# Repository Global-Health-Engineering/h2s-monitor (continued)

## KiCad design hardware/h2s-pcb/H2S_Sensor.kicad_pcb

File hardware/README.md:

# Hardware

All hardware design files for the H2S sensor system, including the custom PCB and the 3D-printed enclosure and gas flow chamber.

## Structure

```
hardware/
├── design/
└── testing/
```

## System Overview

The hardware consists of three main physical components:

**Custom PCB** — designed in KiCad and manufactured by JLCPCB. Integrates the Seeed XIAO ESP32-C6 microcontroller, TI LMP91002 electrochemical analog front end, TI ADS1115 16-bit ADC, DS3232M RTC, SSD1306 OLED display, TI BQ25185 power management IC (USB-C charging, battery protection), MicroSD card slot, and N-channel MOSFET pump driver.

**3D-printed enclosure** — two-part PLA shell (bottom houses PCB, top carries display). Openings provide access to USB-C port, power button, MicroSD slot, and tube connectors.

**3D-printed flow chamber** — cylindrical chamber that seals around the electrochemical sensor body via an O-ring. A small internal cavity between the sensor face and the chamber top is flushed continuously by the diaphragm pump. Must be printed in resin for a gas-tight seal in field deployment; PLA is acceptable for bench testing only.

## Known Issues

- PCB revision V5 has a routing error on two of the four SPI lines to the MicroSD card, causing a short circuit that prevents SD card communication. SD logging is non-functional until corrected in the next revision.

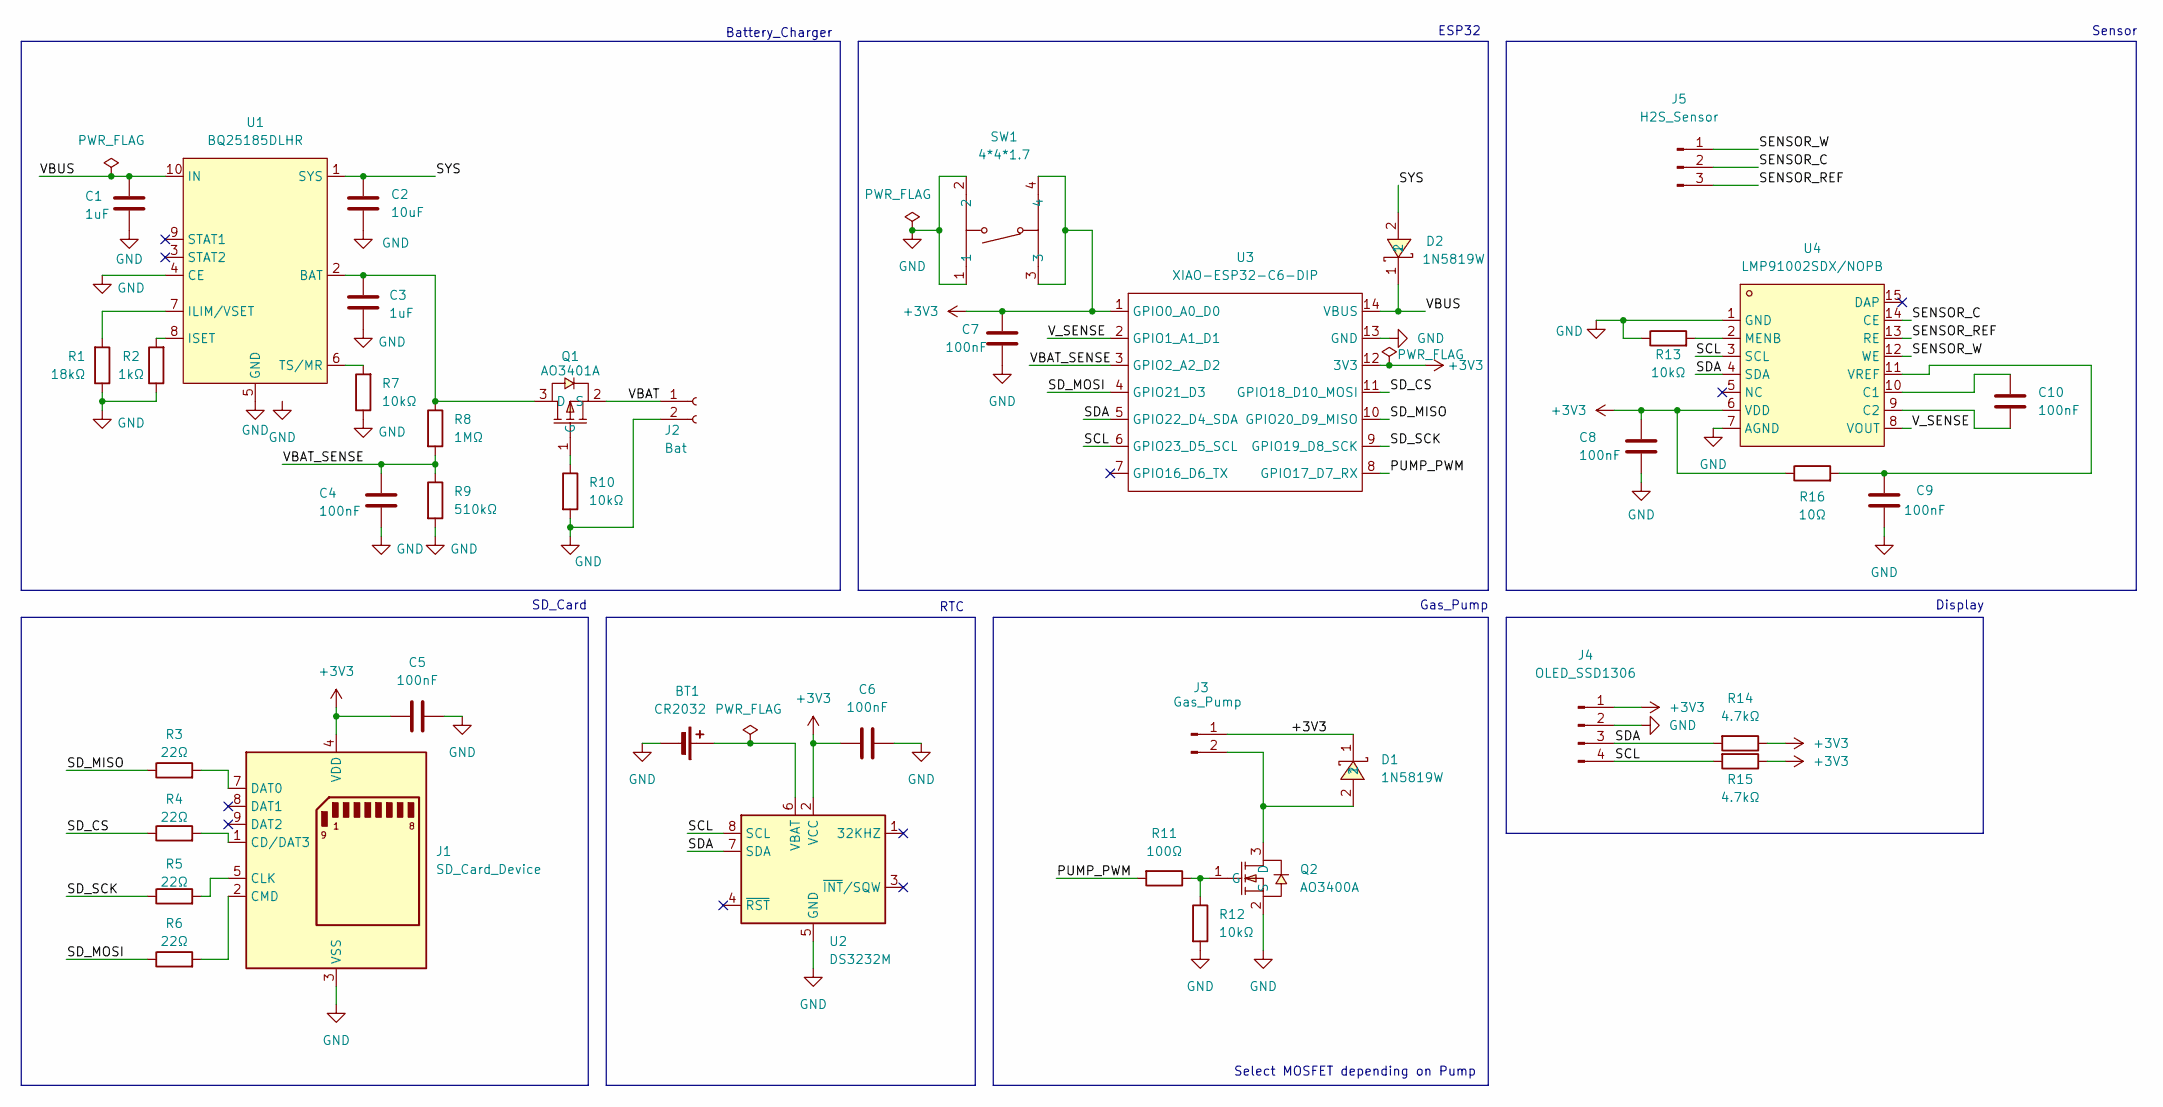
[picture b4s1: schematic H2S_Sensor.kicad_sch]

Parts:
BT1: CR2032; BAT-TH_CR2032-BS-6-1; LCSC Part C70377
C1, C3: 1uF; C_0603_1608Metric; LCSC Part C15849
C2: 10uF; C_0603_1608Metric; LCSC Part C96446
C4, C5, C6, C7, C8, C9, C10: 100nF; C_0603_1608Metric; LCSC Part C14663
D1, D2: 1N5819W; SOD-123F_L2.8-W1.8-LS3.7-RD; MPN 1N5819W; LCSC Part C169540
J1: SD_Card_Device; TF-SMD_TF-15-15; LCSC Part C111196
J2: Bat; Hirose_DF13-02P-1.25DSA_1x02_P1.25mm_Vertical
J3: Gas_Pump; Hirose_DF13-02P-1.25DSA_1x02_P1.25mm_Vertical
J4: OLED_SSD1306; Hirose_DF13-04P-1.25DSA_1x04_P1.25mm_Vertical
J5: H2S_Sensor; H2S_Sensor_3Pin_D20mm
Q1: AO3401A; SOT-23_L2.9-W1.3-P1.90-LS2.4-BR; MPN AO3401A; LCSC Part C15127
Q2: AO3400A; SOT-23-3_L2.9-W1.3-P1.90-LS2.4-BR; MPN AO3400A; LCSC Part C20917
R1: 18kΩ; R_0603_1608Metric; LCSC Part C25810
R2: 1kΩ; R_0603_1608Metric; LCSC Part C21190
R3, R4, R5, R6: 22Ω; R_0603_1608Metric; LCSC Part C23345
R7, R10, R12, R13: 10kΩ; R_0603_1608Metric; LCSC Part C25804
R8: 1MΩ; R_0603_1608Metric; LCSC Part C22935
R9: 510kΩ; R_0603_1608Metric; LCSC Part C23192
R11: 100Ω; R_0603_1608Metric; LCSC Part C22775
R14, R15: 4.7kΩ; R_0603_1608Metric; LCSC Part C23162
R16: 10Ω; R_0603_1608Metric; LCSC Part C22859
SW1: 4*4*1.7; SW-SMD_4P-L5.2-W5.2-P3.70-LS6.5; MPN 4*4*1.7 贴片; LCSC Part C10852
U1: BQ25185DLHR; WSON-10_L2.2-W2.0-P0.40-BL-EP_TI_DLH0010A; LCSC C19725033
U2: DS3232M; SOIC-8_3.9x4.9mm_P1.27mm; LCSC Part C2651581
U3: XIAO-ESP32-C6-DIP
U4: LMP91002SDX/NOPB; WSON-14_L4.0-W4.0-P0.50-BL-EP; MPN LMP91002SDX/NOPB; LCSC Part C2651581

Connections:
+3V3: C5.1, C6.2, C7.1, C8.1, D1.1, J1.4 (VDD), J3.1, J4.1, R14.1, R15.1, R16.1, SW1.3, SW1.4, U2.2 (VCC), U3.1 (GPIO0_A0_D0), U3.12 (3V3), U4.6 (VDD)
/PUMP_PWM: R11.2, U3.8 (GPIO17_D7_RX)
/SCL: J4.4, R15.2, U2.8 (SCL), U3.6 (GPIO23_D5_SCL), U4.3 (SCL)
/SDA: J4.3, R14.2, U2.7 (SDA), U3.5 (GPIO22_D4_SDA), U4.4 (SDA)
/SD_CS: R4.1, U3.11 (GPIO18_D10_MOSI)
/SD_MISO: R3.1, U3.10 (GPIO20_D9_MISO)
/SD_MOSI: R6.1, U3.4 (GPIO21_D3)
/SD_SCK: R5.1, U3.9 (GPIO19_D8_SCK)
/SENSOR_C: J5.2, U4.14 (CE)
/SENSOR_REF: J5.3, U4.13 (RE)
/SENSOR_W: J5.1, U4.12 (WE)
/SYS: C2.1, D2.2, U1.1 (SYS)
/VBAT: J2.1, Q1.2 (S)
/VBAT_SENSE: C4.1, R8.2, R9.1, U3.3 (GPIO2_A2_D2)
/VBUS: C1.2, D2.1, U1.10 (IN), U3.14 (VBUS)
/V_SENSE: U3.2 (GPIO1_A1_D1), U4.8 (VOUT)
GND: BT1.2 (-), C1.1, C2.2, C3.1, C4.2, C5.2, C6.1, C7.2, C8.2, C9.2, J1.3 (VSS), J1.6 (VSS), J2.2, J4.2, Q2.2 (S), R1.1, R2.1, R7.1, R9.2, R10.2, R12.2, R13.1, SW1.1, SW1.2, U1.4 (CE), U1.5 (GND), U1.11 (VSS), U2.5 (GND), U3.13 (GND), U4.1 (GND), U4.7 (AGND), U4.15 (DAP)
unnamed: BT1.1 (+), U2.6 (VBAT)
unnamed: J1.1 (CD/DAT3), R4.2
unnamed: J1.5 (CLK), R5.2
unnamed: J1.2 (CMD), R6.2
unnamed: J1.7 (DAT0), R3.2
unnamed: D1.2, J3.2, Q2.3 (D)
unnamed: C3.2, Q1.3 (D), R8.1, U1.2 (BAT)
unnamed: Q1.1 (G), R10.1
unnamed: Q2.1 (G), R11.1, R12.1
unnamed: R1.2, U1.7 (ILIM/VSET)
unnamed: R2.2, U1.8 (ISET)
unnamed: R7.2, U1.6 (TS/MR)
unnamed: C10.1, U4.10 (C1)
unnamed: C10.2, U4.9 (C2)
unnamed: R13.2, U4.2 (MENB)
unnamed: C9.1, R16.2, U4.11 (VREF)

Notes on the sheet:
Gas_Pump
Sensor
ESP32
Display
RTC
Select MOSFET depending on Pump
SD_Card
Battery_Charger

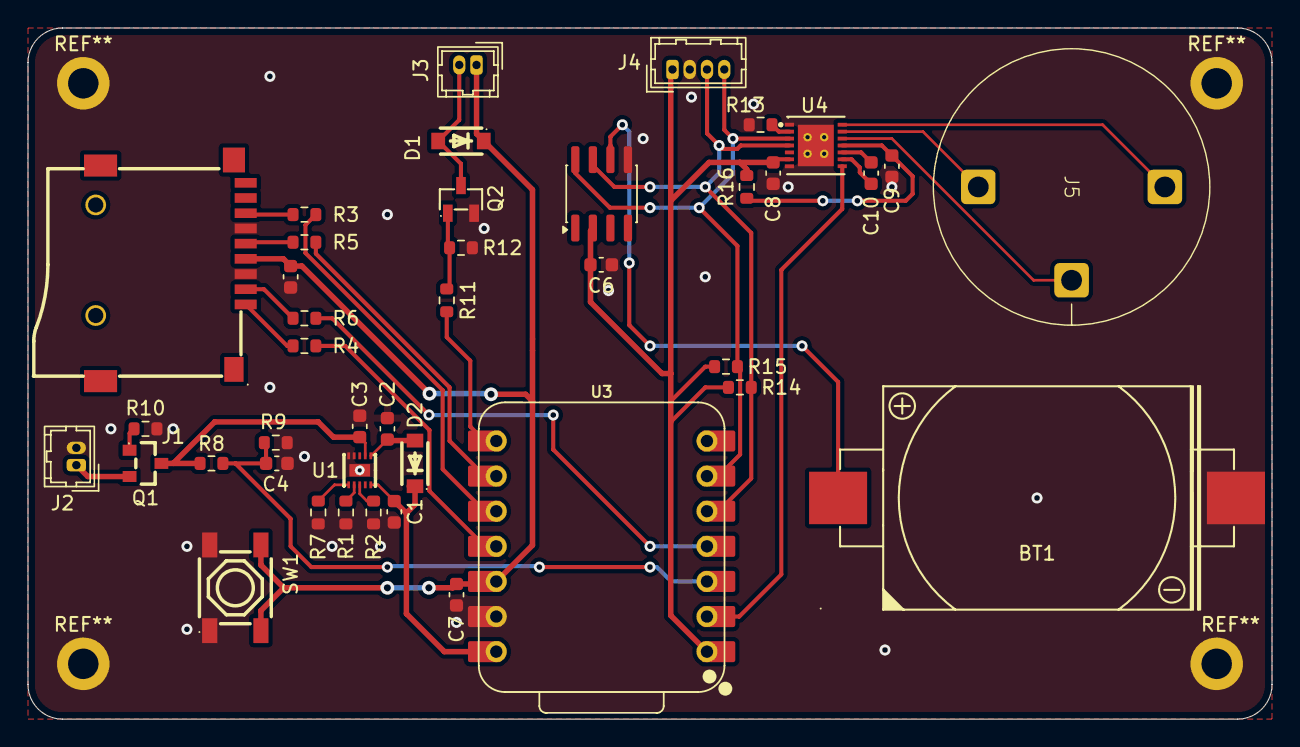
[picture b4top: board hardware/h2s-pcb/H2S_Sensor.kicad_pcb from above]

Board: 2 copper layers, 90.0 x 50.0 mm, 41 parts (0 on the bottom side), 33 nets.

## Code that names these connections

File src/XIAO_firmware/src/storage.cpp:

#include "storage.h"
#include "app_config.h"
#include "sample.h"
#include "queues.h"
#include "rtc.h"
#include "freertos/FreeRTOS.h"
#include "freertos/task.h"
#include "driver/spi_common.h"
#include "driver/sdspi_host.h"
#include "driver/gpio.h"
#include "esp_vfs_fat.h"
#include "sdmmc_cmd.h"
#include <stdio.h>
#include <string.h>
#include "esp_log.h"
#include "nvs_flash.h"
#include "nvs.h"

#define SD_MISO  GPIO_NUM_20
#define SD_CS    GPIO_NUM_18
#define SD_SCK   GPIO_NUM_19
#define SD_MOSI  GPIO_NUM_21
#define MOUNT_PT "/sdcard"

static const char *TAG = "storage";

static char   s_filename[64];
static bool   s_mounted = false;

// Returns a monotonic boot count stored in NVS.
static uint32_t get_boot_count(void) {
    nvs_handle_t h;
    uint32_t count = 0;
    if (nvs_open("storage", NVS_READWRITE, &h) == ESP_OK) {
        nvs_get_u32(h, "boot_cnt", &count);
        nvs_set_u32(h, "boot_cnt", count + 1);
        nvs_commit(h);
        nvs_close(h);
    }
    return count;
}

static bool mount_sd(void) {
    esp_log_level_set("sdmmc", ESP_LOG_VERBOSE);
    esp_log_level_set("sdspi_transaction", ESP_LOG_VERBOSE);
    esp_log_level_set("sdspi_host", ESP_LOG_VERBOSE);

    // GPIO sanity check — log pin levels before handing off to SPI driver.
    gpio_set_direction(SD_CS,   GPIO_MODE_OUTPUT);
    gpio_set_direction(SD_MISO, GPIO_MODE_INPUT);
    gpio_set_pull_mode(SD_MISO, GPIO_PULLUP_ONLY);
    gpio_set_pull_mode(SD_CS,   GPIO_PULLUP_ONLY);
    gpio_set_level(SD_CS, 1);
    vTaskDelay(pdMS_TO_TICKS(10));
    ESP_LOGI(TAG, "GPIO pre-SPI: CS(%d)=%d  MISO(%d)=%d  SCK(%d)=input  MOSI(%d)=input",
             SD_CS,   gpio_get_level(SD_CS),
             SD_MISO, gpio_get_level(SD_MISO),
             SD_SCK,  SD_MOSI);
    vTaskDelay(pdMS_TO_TICKS(500));

    esp_vfs_fat_sdmmc_mount_config_t mount_cfg = {
        .format_if_mount_failed   = false,
        .max_files                = 4,
        .allocation_unit_size     = 16 * 1024,
        .disk_status_check_enable = false,
        .use_one_fat              = false,
    };

    sdmmc_host_t host = SDSPI_HOST_DEFAULT();
    host.max_freq_khz = 400;  // 400 kHz — SD spec minimum for init

    spi_bus_config_t bus_cfg = {};
    // ESP-IDF/C++ compatibility: use data0/data1 aliases instead of mosi/miso designated init.
    bus_cfg.data0_io_num   = SD_MOSI; // MOSI
    bus_cfg.data1_io_num   = SD_MISO; // MISO
    bus_cfg.sclk_io_num    = SD_SCK;
    bus_cfg.quadwp_io_num  = -1;
    bus_cfg.quadhd_io_num  = -1;
    bus_cfg.max_transfer_sz = 4096;
    esp_err_t ret = spi_bus_initialize((spi_host_device_t)host.slot, &bus_cfg, SDSPI_DEFAULT_DMA);
    if (ret != ESP_OK) {
        ESP_LOGE(TAG, "SPI bus init failed: %s", esp_err_to_name(ret));
        return false;
    }

    sdspi_device_config_t slot_cfg = SDSPI_DEVICE_CONFIG_DEFAULT();
    slot_cfg.gpio_cs = SD_CS;
    slot_cfg.host_id = (spi_host_device_t)host.slot;

    sdmmc_card_t *card;
    ret = esp_vfs_fat_sdspi_mount(MOUNT_PT, &host, &slot_cfg, &mount_cfg, &card);
    if (ret != ESP_OK) {
        ESP_LOGE(TAG, "Mount failed: %s", esp_err_to_name(ret));
        spi_bus_free((spi_host_device_t)host.slot);
        return false;
    }
    return true;
}

void storage_init(void) {
    esp_err_t ret = nvs_flash_init();
    if (ret == ESP_ERR_NVS_NO_FREE_PAGES || ret == ESP_ERR_NVS_NEW_VERSION_FOUND) {
        nvs_flash_erase();
        nvs_flash_init();
    }

    s_mounted = mount_sd();
    if (!s_mounted) {
        ESP_LOGE(TAG, "SD card not available");
        return;
    }

    char stem[32];
    rtc_format_filename(stem, sizeof(stem));
    if (strcmp(stem, "log_UNKNOWN") == 0) {
        // RTC not available — fall back to boot counter
        uint32_t boot = get_boot_count();
        snprintf(stem, sizeof(stem), "log_%04lu", (unsigned long)boot);
    }
    snprintf(s_filename, sizeof(s_filename), MOUNT_PT "/%s.csv", stem);

    FILE *f = fopen(s_filename, "w");
    if (f) {
        fprintf(f, "datetime,timestamp_ms,ppm,temperature_c,battery_mv,status\n");
        fclose(f);
    } else {
        ESP_LOGE(TAG, "Could not create log file");
        s_mounted = false;
    }
}

static void write_sample(const sample_t *s) {
    FILE *f = fopen(s_filename, "a");
    if (!f) {
        ESP_LOGE(TAG, "fopen failed");
        return;
    }
    fprintf(f, "%04d-%02d-%02d %02d:%02d:%02d,%llu,%.3f,%.2f,%lu,%lu\n",
            s->datetime.tm_year + 1900, s->datetime.tm_mon + 1, s->datetime.tm_mday,
            s->datetime.tm_hour, s->datetime.tm_min, s->datetime.tm_sec,
            (unsigned long long)s->timestamp,
            s->ppb,
            s->temperature,
            (unsigned long)s->battery_mv,
            (unsigned long)s->status);
    fclose(f);  // flush by close; reopen next sample
}

void storage_task(void *pvParameter) {
    (void)pvParameter;
    sample_t s = {};

    for (;;) {
        if (q_storage && xQueueReceive(q_storage, &s, portMAX_DELAY) == pdTRUE) {
            printf("DATA,%04d-%02d-%02d %02d:%02d:%02d,%llu,%.3f,%.2f,%lu,%lu\n",
                   s.datetime.tm_year + 1900, s.datetime.tm_mon + 1, s.datetime.tm_mday,
                   s.datetime.tm_hour, s.datetime.tm_min, s.datetime.tm_sec,
                   (unsigned long long)s.timestamp,
                   s.ppb, s.temperature,
                   (unsigned long)s.battery_mv,
                   (unsigned long)s.status);

            if (!s_mounted) {
                ESP_LOGE(TAG, "SD not mounted, skipping sample");
                continue;
            }
            if (sd_mutex && xSemaphoreTake(sd_mutex, portMAX_DELAY) == pdTRUE) {
                write_sample(&s);
                xSemaphoreGive(sd_mutex);
            }
            ESP_LOGI(TAG, "#%lu ts=%llums ppm=%.3f temp=%.1fC batt=%lumV status=0x%lx",
                     (unsigned long)s.seq,
                     (unsigned long long)s.timestamp,
                     s.ppb,
                     s.temperature,
                     (unsigned long)s.battery_mv,
                     (unsigned long)s.status);
        }
    }
}

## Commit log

2026-04-27 add pcb v2
2026-04-27 sensor documentation
2026-04-27 v2 pcb review comments
2026-04-27 add gitignore
2026-04-28 small update to review
2026-05-28 Remove all files
2026-05-28 Add H2S sensor PCB design files as pcb_design
2026-05-28 Remove invoice.pdf from pcb_design
2026-06-04 Add GHE project template folder structure
2026-06-04 Move pcb_design into hardware/design/pcb
2026-06-04 Remove placeholder template files
2026-06-04 Restore folder structure and README files
2026-06-04 Add CAD design files to hardware/design/case_CAD
2026-06-04 Move CAD_design.png to media/photo
2026-06-04 Add XIAO firmware to src and raw sensor data to data/raw_data
2026-06-04 Move CSV to raw_data/baseline_stability and rename XIAO_firmware to firmware
2026-06-04 Add baseline stability analysis script and timeseries plot
2026-06-04 Remove timeseries figure and rename script to baseline.py
2026-06-04 Add proposal documents to docs/proposal
2026-06-04 Move proposal files from docs/proposal to docs/reports
2026-06-04 Add PCB photos to media/photo
2026-06-04 Add schematic PDF and device photos to media/photo
2026-06-04 Update tree.txt with current repo structure
2026-06-04 Write all README files with project-specific content
2026-06-04 Remove inline comments from tree structures in README files
2026-06-05 Add final manuscript submission to docs/reports
2026-06-05 Update docs/reports README with final manuscript entries
